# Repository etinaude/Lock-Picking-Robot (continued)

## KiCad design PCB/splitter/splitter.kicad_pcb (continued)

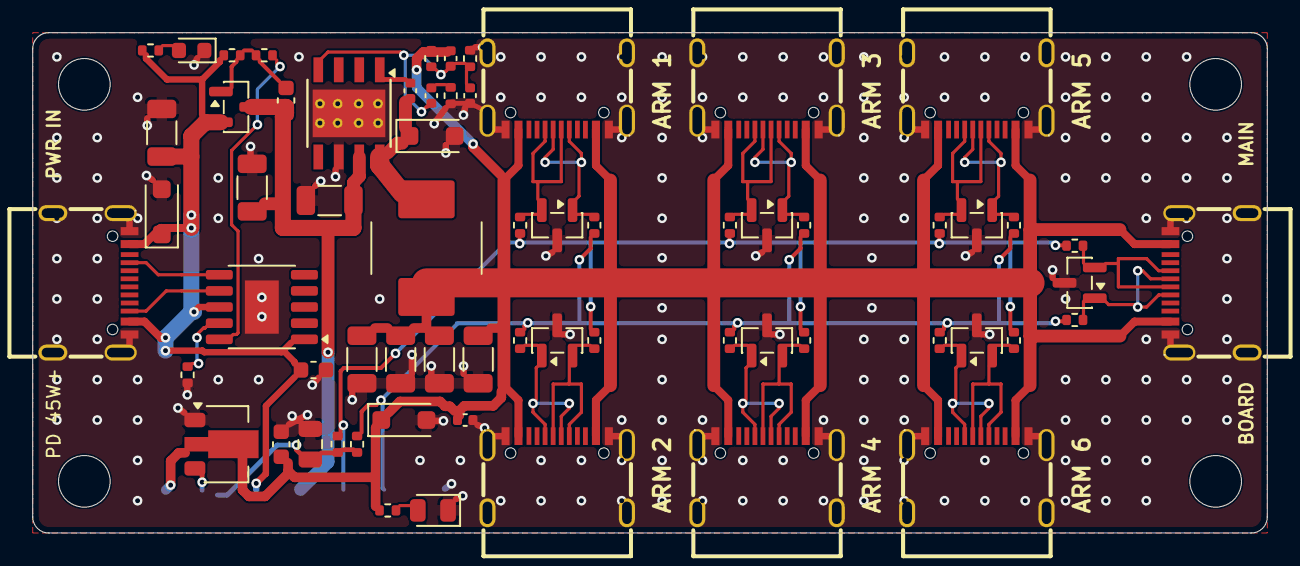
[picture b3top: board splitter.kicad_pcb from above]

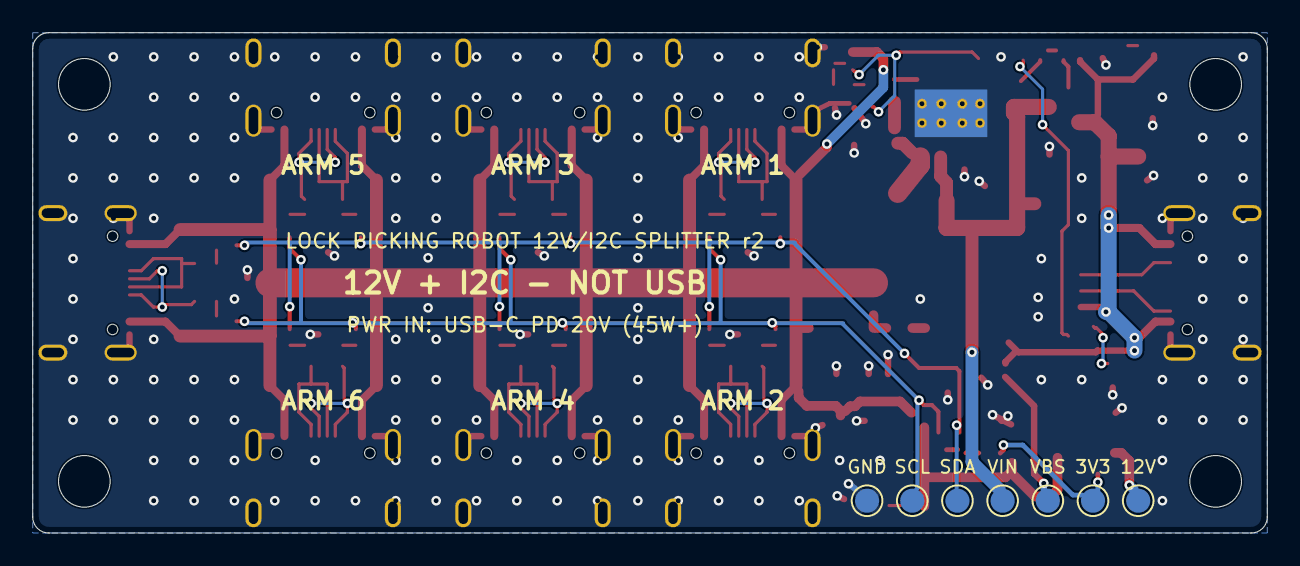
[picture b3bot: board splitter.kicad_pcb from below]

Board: 2 copper layers, 76.5 x 31.0 mm, 76 parts (7 on the bottom side), 32 nets.

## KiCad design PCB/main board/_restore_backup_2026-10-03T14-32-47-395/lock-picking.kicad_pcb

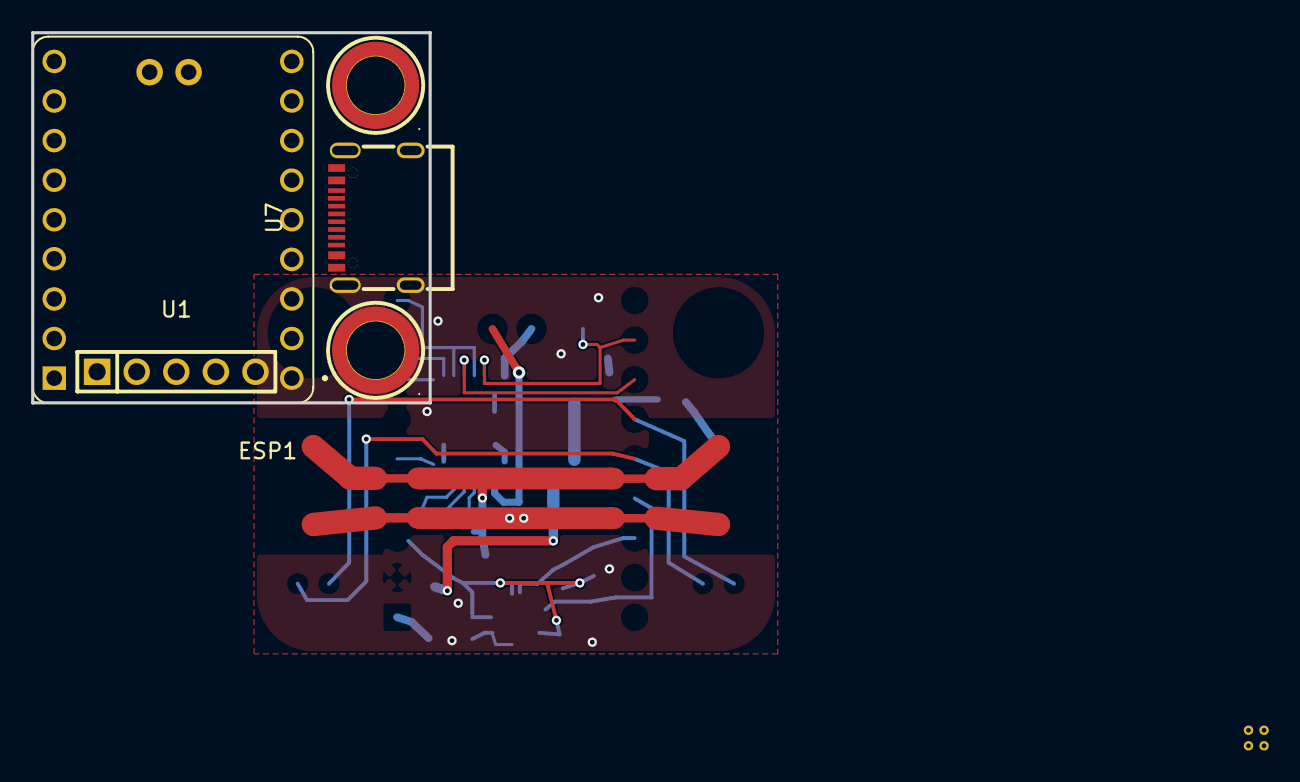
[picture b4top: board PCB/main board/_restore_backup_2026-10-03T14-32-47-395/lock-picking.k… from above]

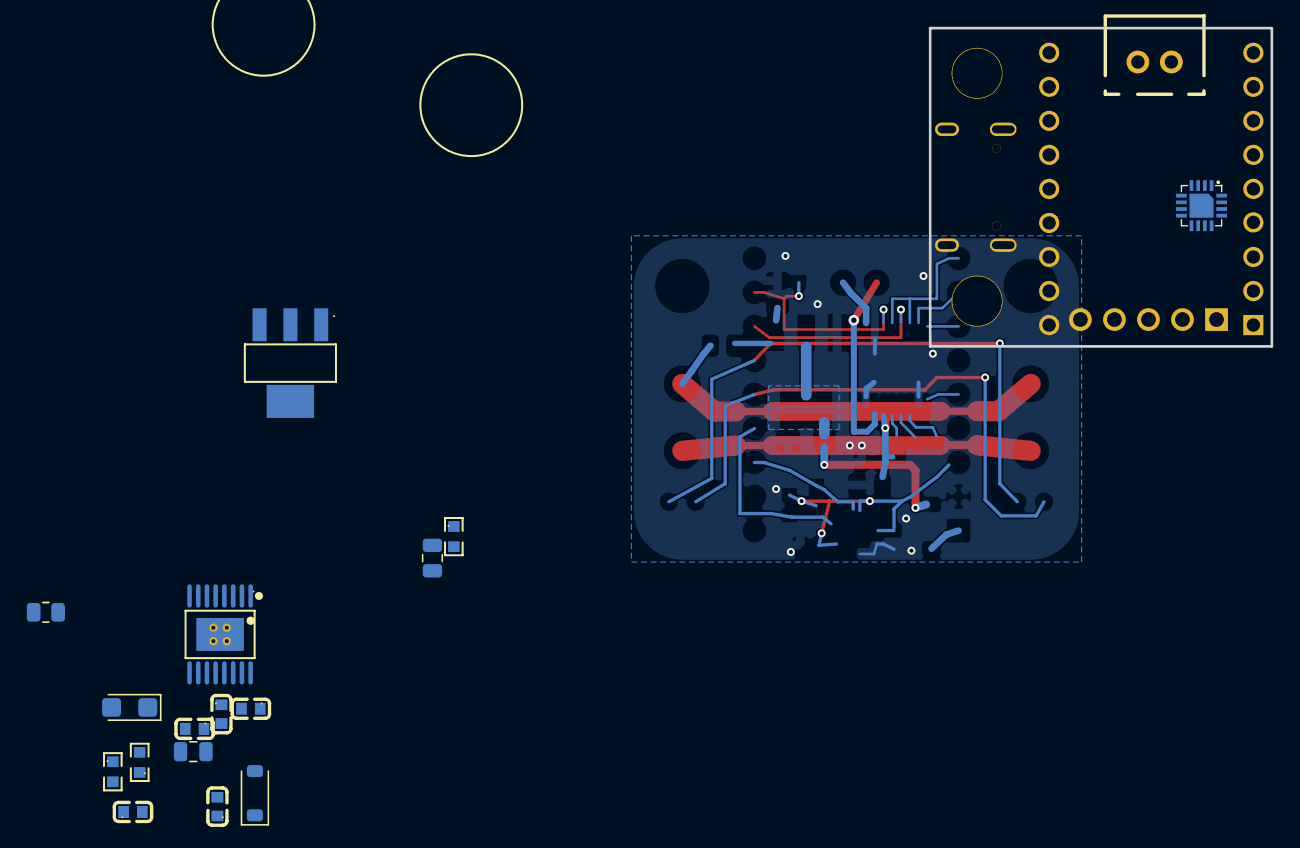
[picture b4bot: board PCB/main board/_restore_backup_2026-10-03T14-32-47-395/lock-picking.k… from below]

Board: 2 copper layers, 25.5 x 23.8 mm, 22 parts (17 on the bottom side), 24 nets.

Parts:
C2, C4, C8, C9: CC0603KRX7R9BB104; C0603
C3: CL10B223KB8NNNC-22nF; C0603
C5, C7: 10uF 25V; C_0805_2012Metric
C6: 10uF 16V tant; CP_EIA-3216-18_Kemet-A
CN1: B2B-XH-A; CONN-TH_B2B-XH-A-LF-SN
D1: B5819W; D_SOD-123
ESP1: ESP32-S3-SuperMini
R2: 0603WAF1501T5E; R0603
R3, R4: 10k; R0603
R5: 10; R_0805_2012Metric
U1: HX PZ2.54-1X5P ZZ; HDR-TH_5P-P2.54-V-M
U2: DRV8876PWPR; HTSSOP-16_L5.0-W4.4-P0.65-LS6.4-BL-EP
U3: MLX90393SLW-ABA-011-RE; VQFN-16_L3.0-W3.0-P0.50-BL-EP1.7
U4, U6: SMTSOM225BTR; SMD_BD5.6-D3.6
U5: AMS1117-5.0; SOT-223_L6.5-W3.5-P2.30-LS7.0-BR
U7: HX TYPE-C 16PIN; TYPE-C-SMD_HX-TYPE-C-16PIN

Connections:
3v3: C8.2, C9.2, ESP1.3V3, R3.1, R4.1, U3.2 (SENB/CS), U3.8 (VDD_IO), U3.15 (VDD)
5v: C6.1, D1.2 (A), U5.2 (VOUT), U5.4 (VOUT)
12v: C2.1, C4.2, C7.1, R5.2, U2.11 (VM)
GND: C2.2, C5.2, C6.2, C7.2, C8.1, C9.1, ESP1.GND, R2.1, U1.2, U2.7 (IMODE), U2.9 (PGND), U2.15 (GND), U2.17 (EP), U3.11 (A1), U3.12 (A0), U3.13 (VSS), U5.1 (GND), U7.A12B1 (GND), U7.B12A1 (GND)
GPIO7: ESP1.7 (GPIO7), U1.5
GPIO8: ESP1.8 (GPIO8), U1.4
GPIO9: ESP1.9 (GPIO9), U1.3
IN1: ESP1.5 (GPIO5), U2.1 (EN/IN1)
IN2: ESP1.4 (GPIO4), U2.2 (PH/IN2)
IPROPI: ESP1.2 (GPIO2), R2.2, U2.6 (IPROPI)
MAG_SCL: ESP1.10 (GPIO10), R4.2, U3.3 (SCL/SCLK)
MAG_SDA: ESP1.11 (GPIO11), R3.2, U3.5 (SDA/MOSI)
unnamed: C3.2, U2.13 (CPH)
unnamed: C3.1, U2.14 (CPL)
unnamed: CN1.2, U2.8 (OUT1)
unnamed: CN1.1, U2.10 (OUT2)
unnamed: C4.1, U2.12 (VCP)
PMODE: ESP1.6 (GPIO6), U2.16 (PMODE)
SCL: ESP1.12 (GPIO12), U7.A7 (D-), U7.B7 (D-)
SDA: ESP1.13 (GPIO13), U7.A6 (D+), U7.B6 (D+)
VBUS: D1.1 (K), ESP1.5V, U1.1
VIN_LDO: C5.1, R5.1, U5.3 (VIN), U7.A9B4 (VBUS), U7.B9A4 (VBUS)
nFAULT: ESP1.1 (GPIO1), U2.4 (nFAULT)
nSLEEP: ESP1.3 (GPIO3), U2.3 (nSLEEP), U2.5 (VREF)

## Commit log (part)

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2025-06-03 Update hero image
2026-01-16 Fix typo in README.md
    difficult-to-lick -> difficult-to-pick
2026-01-16 Fix typo in README description of robot functionality
    Corrected a typo from 'difficult-to-lick' to 'difficult-to-pick' in the README.
